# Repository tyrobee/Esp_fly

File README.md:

# Esp_fly
Custom BLDC ESC and an ESP-based flight controller 

Custom Drone Electronics (ESC + ESP Flight Controller)

A fully custom-built drone electronics stack including:
 ESP-based Flight Controller
 30A BLDC Electronic Speed Controller (ESC)

## Overview
This project focuses on building a complete custom drone control system  instead of using off-the-shelf components.

It includes:
ESC design for BLDC motors  
Flight controller using ESP microcontroller  
Schematic + PCB design  
Component selection and optimization  

## Learning & Inspiration
Before building, I explored:
BLDC motor control and ESC architecture  
Flight controller design basics  
Sensor interfacing and control systems  
Open-source projects  

## References
Electronoobs ESC  
BlueESC (SimonK firmware)  
Various open-source drone FC designs  

## Features
Flight Controller
ESP-based microcontroller  
Multiple motor outputs (quad configuration)  
Designed for sensor integration (MPU6050)  
Custom PCB layout  

## ESC
Designed for ~30A current  
3-phase BLDC motor control  
MOSFET-based power stage  
Compact 2-layer PCB  

## PCB Design

 ### Flight Controller

### ESC

## Frame

## Schematics

## 🧾 Bill of Materials (ESP Drone)

| Name                         | Purpose                                      | Qty | Cost (USD) | Link |
|------------------------------|----------------------------------------------|-----|-----------|------|
| Shipping                     | Shipping                                    | 1   | 10.00     | —    |
| AKKFX Mini VTX 5.8G         | Video transmitter                            | 1   | 21.00     | [Link](#) |
| FlySky FS-iA6B Receiver      | Receiver                                     | 1   | 17.00     | [Link](#) |
| ESP PCB and Pads            | Speed controller                             | 1   | 3.81      | [Link](#) |
| FLIGHT CONTROLLER PCB       | Circuit board                                | 1   | 2.00      | [Link](#) |
| 1046 PROPELLERS             | Push air / lift                              | 2   | 1.15      | [Link](#) |
| MOTOR CCW                   | Thrust                                       | 2   | 11.16     | [Link](#) |
| MOTOR CW                    | Thrust                                       | 2   | 11.16     | [Link](#) |
| FS-i6                       | Transmitter                                  | 1   | 45.00     | [Link](#) |
| MPU6050                     | IMU                                          | 1   | 4.15      | [Link](#) |
| XIAO ESP32 S3               | Microcontroller                              | 1   | 8.65      | [Link](#) |
## Acknowledgements

- Open-source ESC community  
- Electronoobs  
- Blue Robotics

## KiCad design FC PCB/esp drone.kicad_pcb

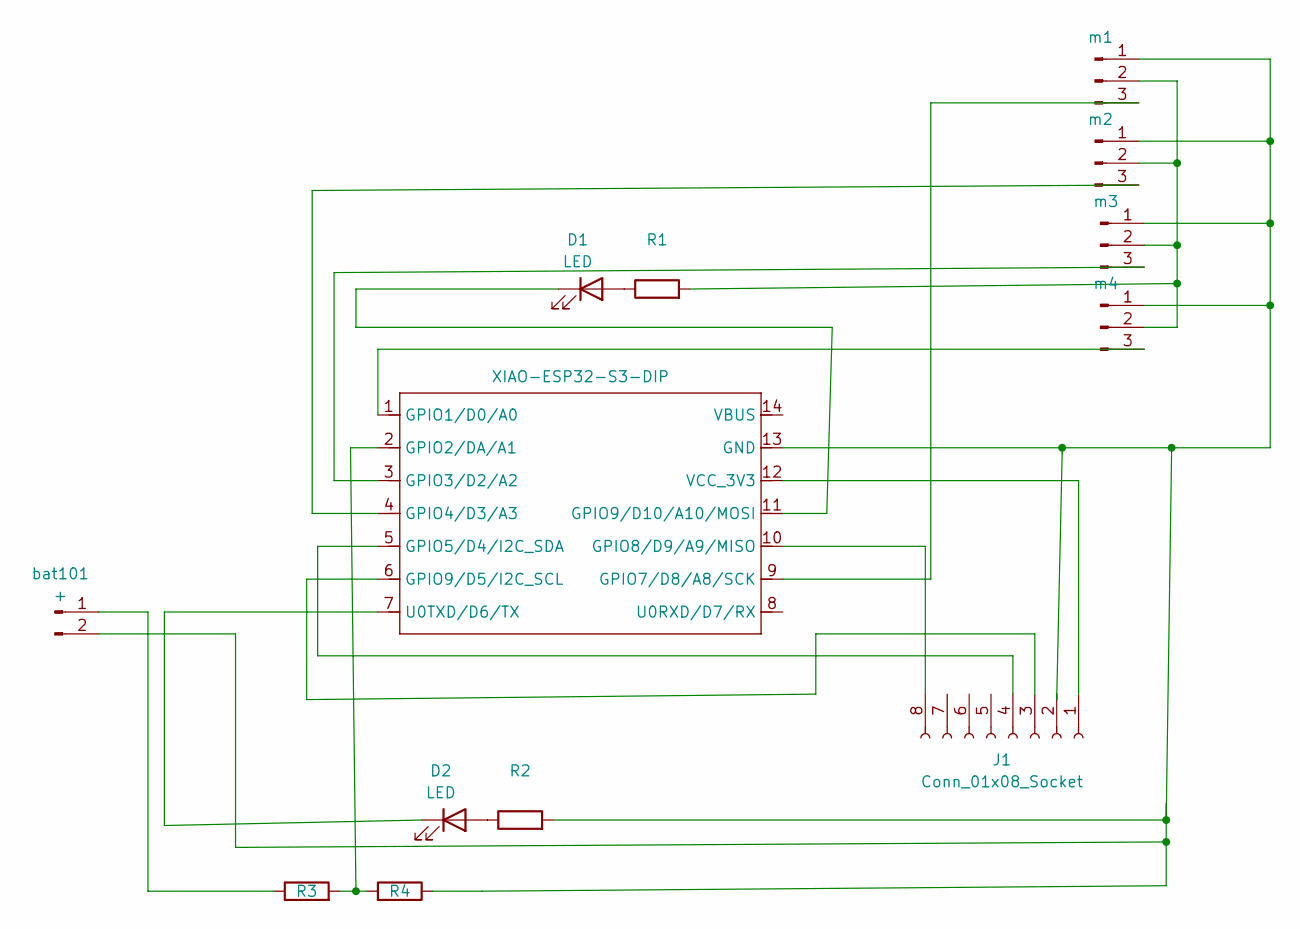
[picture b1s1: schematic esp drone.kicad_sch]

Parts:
D1, D2: LED; LED_D5.0mm
J1: Conn_01x08_Socket; PinHeader_1x08_P2.54mm_Vertical
R1, R2, R3, R4: R; R_Axial_DIN0207_L6.3mm_D2.5mm_P7.62mm_Horizontal
U1: XIAO-ESP32-S3-DIP; MCU_Seeed_ESP32C3
bat101: +; PinHeader_1x02_P2.54mm_Vertical
m1, m2, m3, m4: Conn_01x03_Pin; PinHeader_1x03_P2.54mm_Vertical

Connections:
unnamed: D1.2 (A), R1.1
unnamed: D1.1 (K), U1.11 (GPIO9/D10/A10/MOSI)
unnamed: D2.2 (A), R2.1
unnamed: D2.1 (K), U1.7 (U0TXD/D6/TX)
unnamed: J1.1, U1.12 (VCC_3V3)
unnamed: J1.2, R2.2, R4.1, U1.13 (GND), bat101.2, m1.1, m2.1, m3.1, m4.1
unnamed: J1.3, U1.6 (GPIO9/D5/I2C_SCL)
unnamed: J1.4, U1.5 (GPIO5/D4/I2C_SDA)
unnamed: J1.8, U1.10 (GPIO8/D9/A9/MISO)
unnamed: U1.1 (GPIO1/D0/A0), m4.3
unnamed: R3.2, R4.2, U1.2 (GPIO2/DA/A1)
unnamed: U1.3 (GPIO3/D2/A2), m3.3
unnamed: U1.4 (GPIO4/D3/A3), m2.3
unnamed: U1.9 (GPIO7/D8/A8/SCK), m1.3
unnamed: R3.1, bat101.1
unnamed: R1.2, m1.2, m2.2, m3.2, m4.2

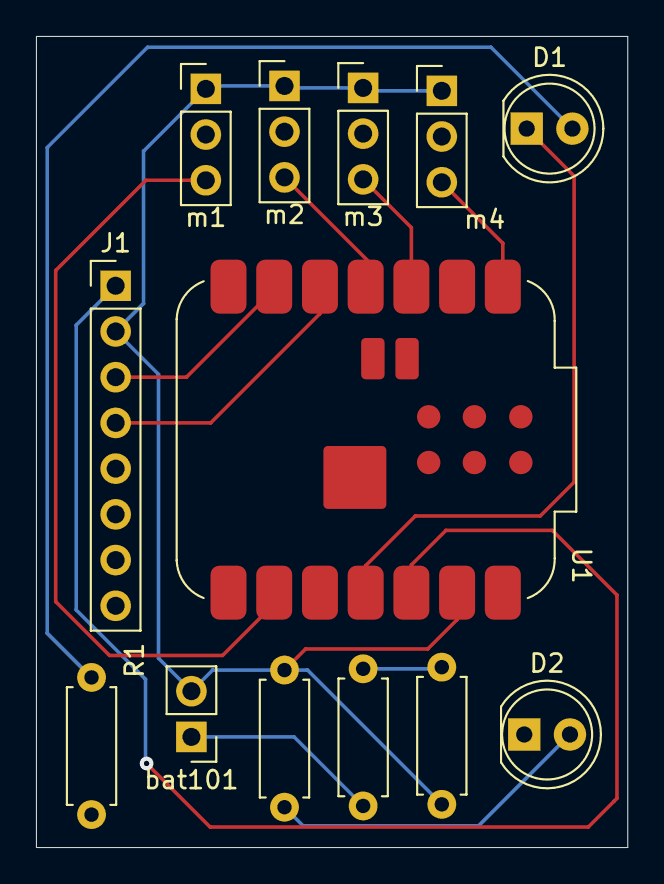
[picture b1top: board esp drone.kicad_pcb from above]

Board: 2 copper layers, 32.9 x 45.1 mm, 13 parts (0 on the bottom side), 16 nets.

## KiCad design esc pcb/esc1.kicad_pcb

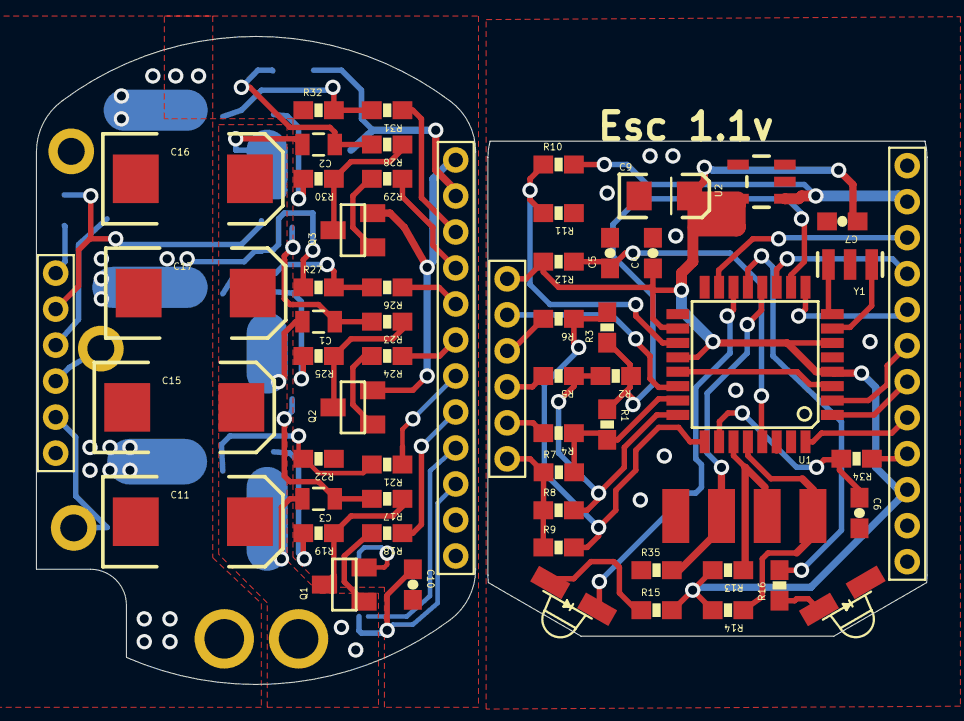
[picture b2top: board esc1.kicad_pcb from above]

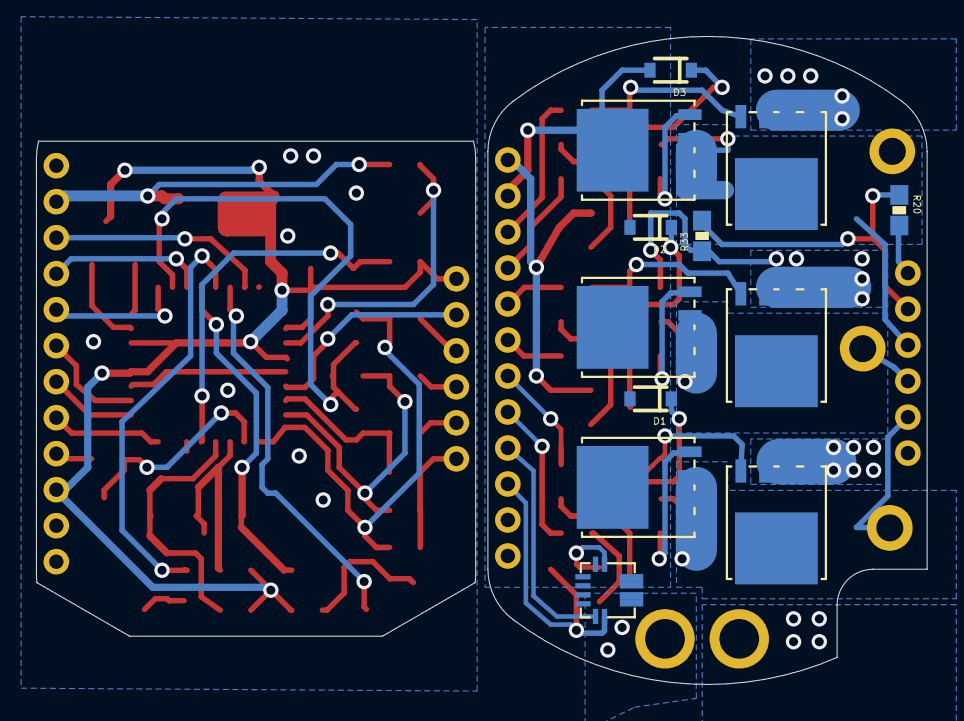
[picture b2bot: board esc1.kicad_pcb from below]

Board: 2 copper layers, 49.5 x 36.0 mm, 79 parts (15 on the bottom side), 61 nets.

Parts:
C1, C2, C3: 1uF 60V; 0805
C4, C5, C7, C10: 0.1uF; 0603-CAP
C6: 1uF; 0603-CAP
C9: 1uF; EIA3216
C11, C15, C16, C17: 100uF; EIA7343
D1, D2, D3: Schottky; SOD-323
LED1: BLUE; SMT-LED-3X2-RA
LED2: RED; SMT-LED-3X2-RA
Q1, Q2, Q3: BC817-40W; SOT23
Q4, Q5, Q6, Q7, Q8, Q9: MOSFET-NCHANNEL; TDSON-8
R1, R2, R3, R4, R5, R6, R34: 47K; 0603-RES
R7, R8, R9, R16, R18, R24, R29: 4.7K; 0603-RES
R10: 18K 1%; 0603-RES
R11, R20: 3.3K 1%; 0603-RES
R12, R13, R14, R22, R27, R32: 10K; 0603-RES
R15: 1K; 0603-RES
R17, R23, R28: 2.2K; 0603-RES
R19, R21, R25, R26, R30, R31: 100; 0603-RES
R33: 10K NTC; 0603-RES
R35: 470K; 0603-RES
U1: ATMEGA168; TQFP32-08
U2: V_REG_LDOSMD; SOT23-5
U$1, U$2: PADPTH-MED; PAD-PTH-MED-1
U$3: ACS7XX12-WFQFN; 12-WFQFN
U$4, U$16: HEADER-62MM; HEADER-2MM-6POS
U$5, U$6, U$7: PAD18AWG; PAD-PTH-18AWG-1
U$8, U$17: HEADER-122MM; HEADER-2MM-12POS
U$11, U$12, U$13, U$14: PAD1.5X3MM; PAD-1.5X3MM
Y1: RESONATORSMD; RESONATOR-SMD

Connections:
CENTER: R1.1, R2.1, R3.1, U1.10
CURRENT_ADC: U$3.VIOUT, U$8.P$4
CURRENT_ADC_FILTERED: C6.1, R34.2, U1.26
GATE_AH: Q4.G, R19.2
GATE_AL: Q5.G, R21.2, R22.2
GATE_BH: Q6.G, R25.2
GATE_BL: Q7.G, R26.2, R27.2
GATE_CH: Q8.G, R30.2
GATE_CL: Q9.G, R31.2, R32.2
GND: C10.2, C11.C, C15.C, C16.C, C17.C, Q1.2, Q2.2, Q3.2, Q5.S1, Q5.S2, Q5.S3, Q7.S1, Q7.S2, Q7.S3, Q9.S1, Q9.S2, Q9.S3, R22.1, R27.1, R32.1, R33.1, U$2.P$1, U$3.GND, U$4.P$1, U$8.P$1, U$8.P$2, U$8.P$12
LED_STATUS: LED1.2, U1.14
LED_WARN: R16.2, U1.13
L_CURRENT_ADC: R34.1, U$17.P$4
L_GND: C4.2, C5.2, C6.2, C7.2, C9.C, LED2.2, R7.1, R8.1, R9.1, R11.1, R35.1, U1.3, U1.5, U1.21, U2.2, U$11.P$1, U$16.P$1, U$17.P$1, U$17.P$2, U$17.P$12, Y1.2
L_PHASE_A: R4.2, U$16.P$2
L_PHASE_B: R5.2, U$16.P$3
L_PHASE_C: R6.2, U$16.P$4
L_PWM_AH: U1.32, U$17.P$5
L_PWM_AL: U1.1, U$17.P$6
L_PWM_BH: U1.2, U$17.P$7
L_PWM_BL: U1.9, U$17.P$8
L_PWM_CH: U1.11, U$17.P$9
L_PWM_CL: U1.15, U$17.P$10
L_TEMP_ADC: U1.22, U$16.P$5
L_VBAT: R10.2, U2.1, U$17.P$11
unnamed: Q1.1, R18.2
unnamed: LED2.1, R16.1
unnamed: Q1.3, R17.1, R19.1
unnamed: Q2.1, R24.2
unnamed: Q2.3, R23.1, R25.1
unnamed: Q3.1, R29.2
unnamed: Q3.3, R28.1, R30.1
unnamed: U1.7, Y1.1
unnamed: U1.8, Y1.3
unnamed: C3.1, D1.C, R17.2
unnamed: C1.1, D2.C, R23.2
unnamed: LED1.1, R15.1
unnamed: C2.1, D3.C, R28.2
PHASE_A: C3.2, Q4.S1, Q4.S2, Q4.S3, Q5.D, U$4.P$2, U$5.P$1
PHASE_B: C1.2, Q6.S1, Q6.S2, Q6.S3, Q7.D, U$4.P$3, U$6.P$1
PHASE_C: C2.2, Q8.S1, Q8.S2, Q8.S3, Q9.D, U$4.P$4, U$7.P$1
PWM: R35.2, U1.12, U$14.P$1
PWM_AH: R18.1, U$8.P$5
PWM_AL: R21.1, U$8.P$6
PWM_BH: R24.1, U$8.P$7
PWM_BL: R26.1, U$8.P$8
PWM_CH: R29.1, U$8.P$9
PWM_CL: R31.1, U$8.P$10
RESET: C5.1, R12.1, U1.29
SCL: R14.1, U1.28, U$13.P$1
SDA: R13.1, U1.27, U$12.P$1
SENSE_A: R1.2, R4.1, R7.2, U1.23
SENSE_B: R2.2, R5.1, R8.2, U1.24
SENSE_C: R3.2, R6.1, R9.2, U1.25
TEMP_ADC: R20.1, R33.2, U$4.P$5
VBAT: D1.A, D2.A, D3.A, Q4.D, Q6.D, Q8.D, U$3.IP-1, U$3.IP-2, U$8.P$11
VBAT+: C11.A, C15.A, C16.A, C17.A, U$1.P$1, U$3.IP+1, U$3.IP+2
VBAT_ADC: R10.1, R11.2, U1.19
VCC5V: C4.1, C7.1, C9.A, R12.2, R13.2, R14.2, R15.2, U1.4, U1.6, U1.18, U1.20, U2.5, U$16.P$6, U$17.P$3
VCC5V-1: R20.2, U$4.P$6
VCC5V-2: C10.1, U$3.VCC, U$8.P$3

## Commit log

2026-03-18 Update README with project details and features
    Expanded project description and added details about features, learning resources, and acknowledgements.
2026-03-18 Restore ESC images in README.md
    Reinsert ESC images in the PCB Design section.
2026-03-22 cad designs
2026-03-30 Revise BOM with updated components and quantities
    Updated BOM section with new component details and specifications.
2026-03-30 Revise BOM with additional components and details
    Updated BOM section with new components and quantities.
2026-04-03 Add schematics section with wiring diagram
2026-04-17 Fix formatting of PCB Design section in README
